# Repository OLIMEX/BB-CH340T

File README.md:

# BB-CH340T

OSHW USB to serial converter with CH340

The board and schematic files are created with KiCad.

Product page: https://www.olimex.com/Products/Breadboarding/BB-CH340T/open-source-hardware

## Licensee
* Hardware is released under CERN Open Hardware Licence Version 2 -
Strongly Reciprocal
* Software is released under GPL3 Licensee
* Documentation is released under CC BY-SA 3.0

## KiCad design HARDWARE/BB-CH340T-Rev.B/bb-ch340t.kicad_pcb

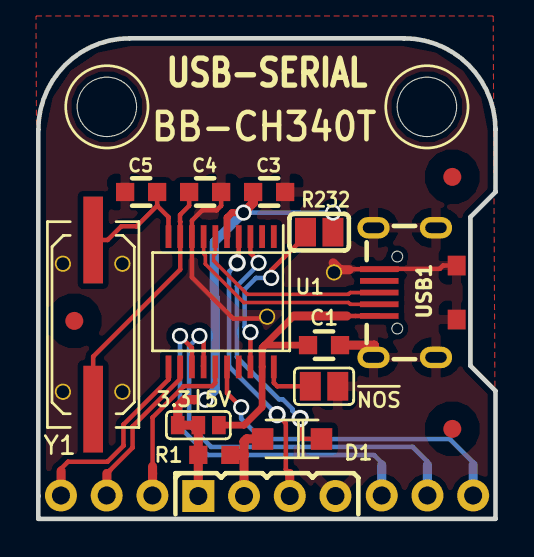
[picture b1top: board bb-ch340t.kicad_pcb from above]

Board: 2 copper layers, 25.4 x 26.7 mm, 21 parts (0 on the bottom side), 19 nets.

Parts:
C1: 2.2uF; C_0603_5MIL_DWS
C3: 10nF; C_0603_5MIL_DWS
C4, C5: 39p; C_0603_5MIL_DWS
CON1, CON2: n.a; HN1x3
D1: 1N5819/S4; SOD-123_KA
JP1: 3.3-5V; SJ_2_SMALL_12_TIED
POUT1: HR1X4; HN1x4
R1: 1K; R_0603_5MIL_DWS
Ref**: Val**; via_09_07
Ref**#2, Ref**#3, Ref**#4, Ref**#5, Ref**#6: Val**; via_09_07
SJ1: #NOS; SJ
SJ2: RS232; SJ
U1: CH340H/T; SSOP-20W
USB1: USB-uicro-B; USB-MICRO_MISB-SWMM-5B_LF
Y1: 12.0MHz; Q_49U3HMS

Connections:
/CTS: CON1.1, U1.11
/DCD: CON2.2, U1.14
/DSR: CON1.2, U1.12
/DTR: CON1.3, U1.15
/D_N: U1.7, USB1.2
/D_P: U1.6, USB1.3
/NOS: SJ1.1, U1.20
/RI: CON2.1, U1.13
/RTS: CON2.3, U1.16
/RXD: POUT1.3, U1.4
/TX: D1.1, U1.3
/TXD: D1.2, POUT1.2, R1.2
/VDD: JP1.2, POUT1.1, R1.1
GND: C1.2, C3.2, C4.2, C5.2, POUT1.4, Ref**.0, Ref**#2.0, Ref**#3.0, Ref**#4.0, Ref**#5.0, Ref**#6.0, SJ1.2, U1.8, USB1.0, USB1.5
unnamed: C1.1, JP1.3, U1.19, USB1.1
unnamed: C3.1, JP1.1, SJ2.2, U1.5
unnamed: C4.1, U1.9, Y1.1
unnamed: C5.1, U1.10, Y1.2
unnamed: SJ2.1, U1.18

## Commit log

2015-06-26 upload CAD files
2015-07-01 Schematic update
2020-04-29 fix structure
2022-01-20 Update
    revision B

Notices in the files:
HARDWARE/BB-CH340T-Rev.B/bb-ch340t.kicad_pcb:
(c) 2018
